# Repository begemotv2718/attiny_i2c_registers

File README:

Implementation of smbus i2c slave with registers on attiny mcu. 

Write register: view from master (slave replies in brackets)
START Addr Wr [ACK] RegNum [ACK] Value [ACK] STOP

Read register: view from master

START Addr Wr [ACK] RegNum [ACK] START Addr Rd [RegValue] NAK STOP

Seems to work for slow transfers (<5kHz).

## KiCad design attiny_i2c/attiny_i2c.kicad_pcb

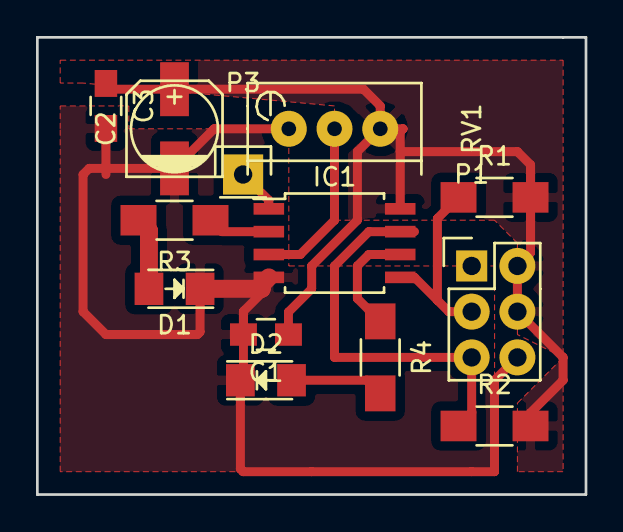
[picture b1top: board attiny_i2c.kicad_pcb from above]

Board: 2 copper layers, 30.5 x 25.4 mm, 13 parts (0 on the bottom side), 10 nets.

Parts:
C1, C3: C_Small; C_0805_HandSoldering
C2: CP_Small; c_elec_5x5.8
D1, D2: Led_Small; LED-1206
IC1: ATTINY25-S; SOIJ-8_5.3x5.3mm_Pitch1.27mm
P1: CONN_02X03; Pin_Header_Straight_2x03
P3: CONN_01X01; Pin_Header_Straight_1x01
R1, R2, R3, R4: R; R_1206_HandSoldering
RV1: POT; Potentiometer_Bourns_3296W_3-8Zoll_Inline_ScrewUp

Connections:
+5V: C1.1, C2.1, C3.1, IC1.8, P1.2, P1.4, R1.2, R2.2, RV1.3
GND: C1.2, C2.2, C3.2, D1.1, D2.1, IC1.4, P1.6, RV1.1
I2C_SCL: IC1.7, P1.5, R2.1
I2C_SDA: IC1.5, P1.3, R1.1
LED1: IC1.2, R3.1
LED2: IC1.6, R4.1
unnamed: D1.2, R3.2
unnamed: D2.2, R4.2
PRG_RST: IC1.1, P3.1
VREG: IC1.3, RV1.2

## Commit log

2018-01-02 Added gitignore
2018-02-08 Something working
2018-02-09 Added README
2018-02-17 Working on 5khz
2018-02-17 Updated information
2018-02-17 Added ADC example
2018-04-17 Schematics
2018-05-05 More or less current schematics
2018-05-06 Current module version
2019-03-19 Modified pcb
2019-03-19 Documentation for example device
